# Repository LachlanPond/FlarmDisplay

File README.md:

# FlarmDisplay
Basic LED Flarm display

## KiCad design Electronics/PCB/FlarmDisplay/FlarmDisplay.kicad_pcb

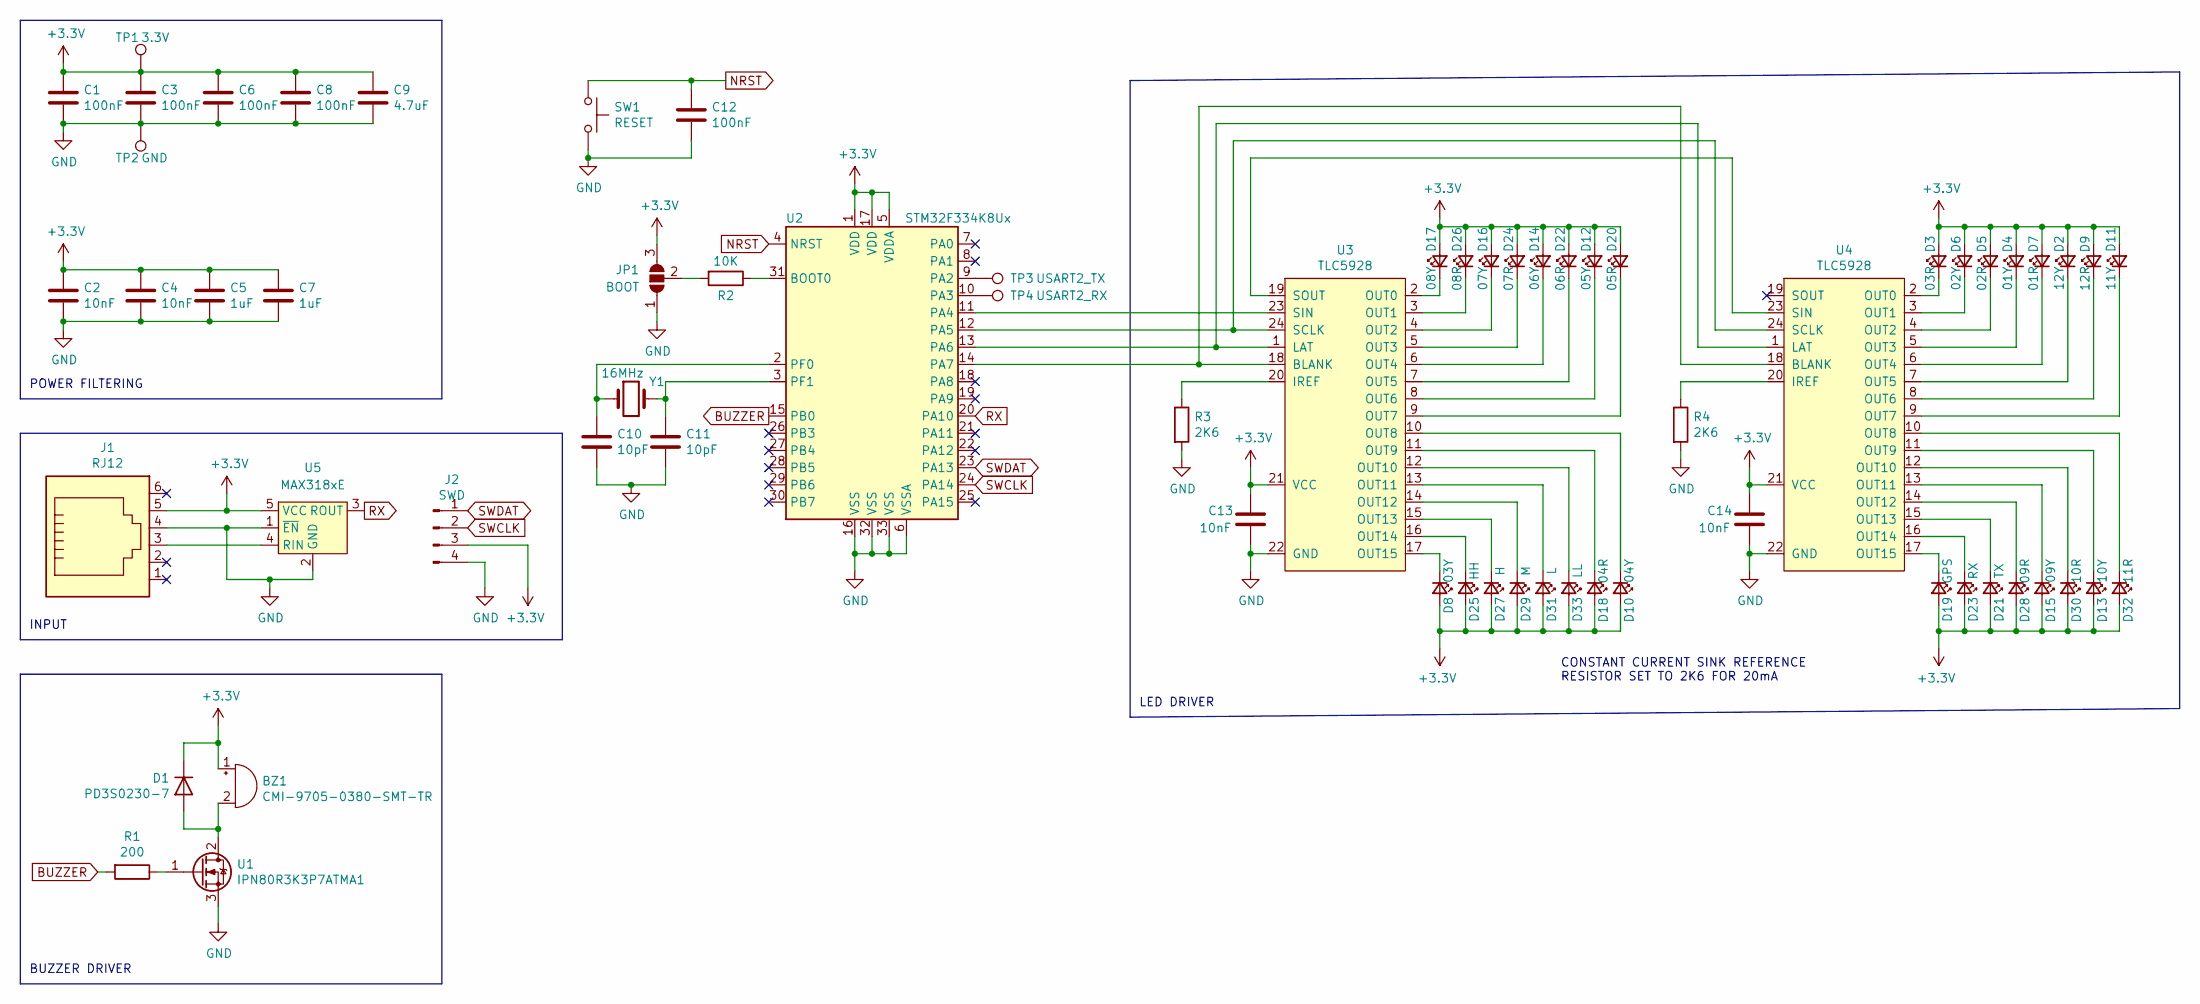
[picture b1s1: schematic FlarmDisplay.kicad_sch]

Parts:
BZ1: CMI-9705-0380-SMT-TR
C1, C3, C6, C8, C12: 100nF; C_0402_1005Metric
C2, C4, C13, C14: 10nF; C_0402_1005Metric
C5, C7: 1uF; C_0402_1005Metric
C9: 4.7uF; C_0805_2012Metric
C10, C11: 10pF; C_0402_1005Metric
D1: PD3S0230-7; POWERDI323
D2: 12Y; LED_0805_2012Metric
D3: 03R; LED_0805_2012Metric
D4: 01Y; LED_0805_2012Metric
D5: 02R; LED_0805_2012Metric
D6: 02Y; LED_0805_2012Metric
D7: 01R; LED_0805_2012Metric
D8: 03Y; LED_0805_2012Metric
D9: 12R; LED_0805_2012Metric
D10: 04Y; LED_0805_2012Metric
D11: 11Y; LED_0805_2012Metric
D12: 05Y; LED_0805_2012Metric
D13: 10Y; LED_0805_2012Metric
D14: 06Y; LED_0805_2012Metric
D15: 09Y; LED_0805_2012Metric
D16: 07Y; LED_0805_2012Metric
D17: 08Y; LED_0805_2012Metric
D18: 04R; LED_0805_2012Metric
D19: GPS; LED_0805_2012Metric
D20: 05R; LED_0805_2012Metric
D21: TX; LED_0805_2012Metric
D22: 06R; LED_0805_2012Metric
D23: RX; LED_0805_2012Metric
D24: 07R; LED_0805_2012Metric
D25: HH; LED_0805_2012Metric
D26: 08R; LED_0805_2012Metric
D27: H; LED_0805_2012Metric
D28: 09R; LED_0805_2012Metric
D29: M; LED_0805_2012Metric
D30: 10R; LED_0805_2012Metric
D31: L; LED_0805_2012Metric
D32: 11R; LED_0805_2012Metric
D33: LL; LED_0805_2012Metric
J1: RJ12; RJE231660413T
J2: SWD; PinHeader_1x04_P2.54mm_Vertical
JP1: BOOT; SolderJumper-3_P1.3mm_Open_RoundedPad1.0x1.5mm
R1: 200; R_0402_1005Metric
R2: 10K; R_0402_1005Metric
R3, R4: 2K6; R_0402_1005Metric
SW1: RESET; SMT_J
TP1: 3.3V; TestPoint_Pad_D2.0mm
TP2: GND; TestPoint_Pad_D2.0mm
TP3: USART2_TX; TestPoint_Pad_D2.0mm
TP4: USART2_RX; TestPoint_Pad_D2.0mm
U1: IPN80R3K3P7ATMA1; SOT-223-3_TabPin2
U2: STM32F334K8Ux; QFN-32-1EP_5x5mm_P0.5mm_EP3.45x3.45mm
U3, U4: TLC5928; VQFN-24-1EP_4x4mm_P0.5mm_EP2.45x2.45mm
U5: MAX318xE; SOT-23-5
Y1: 16MHz; Crystal_SMD_3225-4Pin_3.2x2.5mm

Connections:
+3V3: BZ1.1 (-), C1.1, C2.1, C3.1, C4.1, C5.1, C6.1, C7.1, C8.1, C9.1, C13.1, C14.1, D1.1 (K), D2.2 (A), D3.2 (A), D4.2 (A), D5.2 (A), D6.2 (A), D7.2 (A), D8.2 (A), D9.2 (A), D10.2 (A), D11.2 (A), D12.2 (A), D13.2 (A), D14.2 (A), D15.2 (A), D16.2 (A), D17.2 (A), D18.2 (A), D19.2 (A), D20.2 (A), D21.2 (A), D22.2 (A), D23.2 (A), D24.2 (A), D25.2 (A), D26.2 (A), D27.2 (A), D28.2 (A), D29.2 (A), D30.2 (A), D31.2 (A), D32.2 (A), D33.2 (A), J1.5, J2.3, JP1.3 (B), TP1.1, U2.1 (VDD), U2.5 (VDDA), U2.17 (VDD), U3.21 (VCC), U4.21 (VCC), U5.5 (VCC); also elsewhere on the board
BUZZER: R1.2, U2.15 (PB0)
GND: C1.2, C2.2, C3.2, C4.2, C5.2, C6.2, C7.2, C8.2, C9.2, C10.2, C11.2, C12.2, C13.2, C14.2, J1.4, J2.4, JP1.1 (A), R3.2, R4.2, SW1.2, TP2.1, U1.3, U2.6 (VSSA), U2.16 (VSS), U2.32 (VSS), U2.33 (VSS), U3.22 (GND), U4.22 (GND), U5.1 (~EN), U5.2 (GND)
NRST: C12.1, SW1.1, U2.4 (NRST)
unnamed: BZ1.2 (+), D1.2 (A), U1.2
unnamed: C10.1, U2.2 (PF0), Y1.1
unnamed: C11.1, U2.3 (PF1), Y1.2
unnamed: D2.1 (K), U4.7 (OUT5)
unnamed: D3.1 (K), U4.2 (OUT0)
unnamed: D4.1 (K), U4.5 (OUT3)
unnamed: D5.1 (K), U4.4 (OUT2)
unnamed: D6.1 (K), U4.3 (OUT1)
unnamed: D7.1 (K), U4.6 (OUT4)
unnamed: D8.1 (K), U3.17 (OUT15)
unnamed: D9.1 (K), U4.8 (OUT6)
unnamed: D10.1 (K), U3.10 (OUT8)
unnamed: D11.1 (K), U4.9 (OUT7)
unnamed: D12.1 (K), U3.8 (OUT6)
unnamed: D13.1 (K), U4.11 (OUT9)
unnamed: D14.1 (K), U3.6 (OUT4)
unnamed: D15.1 (K), U4.13 (OUT11)
unnamed: D16.1 (K), U3.4 (OUT2)
unnamed: D17.1 (K), U3.2 (OUT0)
unnamed: D18.1 (K), U3.11 (OUT9)
unnamed: D19.1 (K), U4.17 (OUT15)
unnamed: D20.1 (K), U3.9 (OUT7)
unnamed: D21.1 (K), U4.15 (OUT13)
unnamed: D22.1 (K), U3.7 (OUT5)
unnamed: D23.1 (K), U4.16 (OUT14)
unnamed: D24.1 (K), U3.5 (OUT3)
unnamed: D25.1 (K), U3.16 (OUT14)
unnamed: D26.1 (K), U3.3 (OUT1)
unnamed: D27.1 (K), U3.15 (OUT13)
unnamed: D28.1 (K), U4.14 (OUT12)
unnamed: D29.1 (K), U3.14 (OUT12)
unnamed: D30.1 (K), U4.12 (OUT10)
unnamed: D31.1 (K), U3.13 (OUT11)
unnamed: D32.1 (K), U4.10 (OUT8)
unnamed: D33.1 (K), U3.12 (OUT10)
unnamed: J1.3, U5.4 (RIN)
unnamed: R1.1, U1.1
unnamed: R2.1, U2.31 (BOOT0)
unnamed: JP1.2 (C), R2.2
unnamed: R3.1, U3.20 (IREF)
unnamed: R4.1, U4.20 (IREF)
unnamed 45: TP3.1, U2.9 (PA2); also elsewhere on the board
unnamed 46: TP4.1, U2.10 (PA3); also elsewhere on the board
unnamed: U2.11 (PA4), U3.23 (SIN)
unnamed: U2.12 (PA5), U3.24 (SCLK), U4.24 (SCLK)
unnamed: U2.13 (PA6), U3.1 (LAT), U4.1 (LAT)
unnamed: U2.14 (PA7), U3.18 (BLANK), U4.18 (BLANK)
unnamed: U3.19 (SOUT), U4.23 (SIN)
RX: U2.20 (PA10), U5.3 (ROUT)
SWCLK: J2.2, U2.24 (PA14)
SWDAT: J2.1, U2.23 (PA13)

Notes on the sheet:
INPUT
LED DRIVER
POWER FILTERING
BUZZER DRIVER
CONSTANT CURRENT SINK REFERENCE RESISTOR SET TO 2K6 FOR 20mA

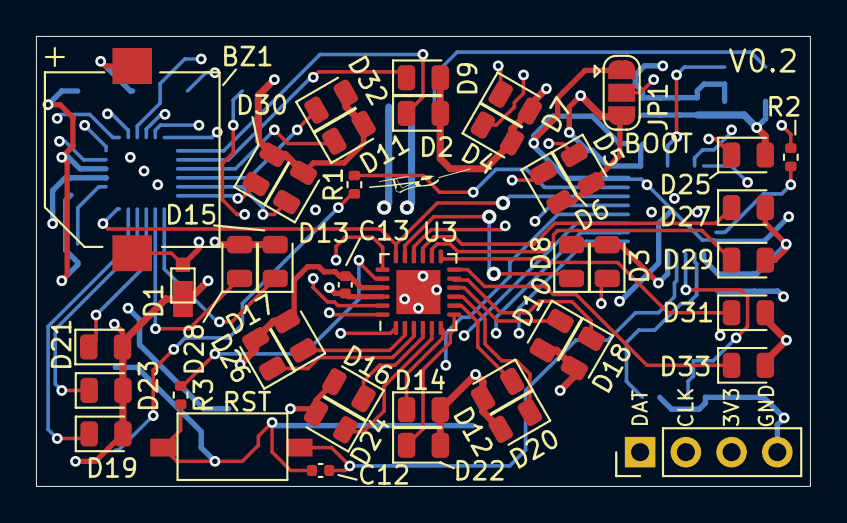
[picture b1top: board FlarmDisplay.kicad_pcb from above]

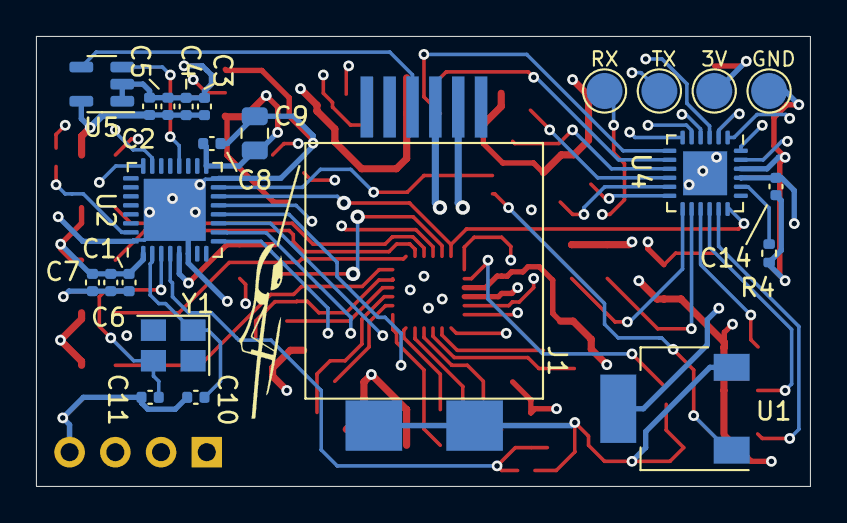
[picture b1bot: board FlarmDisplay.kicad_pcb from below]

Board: 4 copper layers, 43.0 x 25.0 mm, 66 parts (23 on the bottom side), 55 nets.

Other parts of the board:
3V: 3.3V; TestPoint_Pad_D2.0mm
RX: USART2_RX; TestPoint_Pad_D2.0mm
TX: USART2_TX; TestPoint_Pad_D2.0mm

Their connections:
+3V3: 3V.1; also elsewhere on the board
unnamed 45: TX.1; also elsewhere on the board
unnamed 46: RX.1; also elsewhere on the board

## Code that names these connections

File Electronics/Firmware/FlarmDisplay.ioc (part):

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Mcu.Name=STM32F334K(4-6-8)Ux
Mcu.Package=UFQFPN32
Mcu.UserName=STM32F334K8Ux
PA10.Mode=Asynchronous
PA10.Signal=USART1_RX
PA13.Signal=SYS_JTMS-SWDIO
PA14.Signal=SYS_JTCK-SWCLK
PA2.Mode=Asynchronous
PA2.Signal=USART2_TX
PA3.Mode=Asynchronous
PA3.Signal=USART2_RX
PA4.GPIOParameters=PinState,GPIO_PuPd,GPIO_Label
PA4.GPIO_Label=SIN
PA4.GPIO_PuPd=GPIO_PULLDOWN
PA4.PinState=GPIO_PIN_RESET
PA4.Signal=GPIO_Output
PA5.GPIOParameters=PinState,GPIO_PuPd,GPIO_Label
PA5.GPIO_Label=SCLK
PA5.GPIO_PuPd=GPIO_PULLDOWN
PA5.PinState=GPIO_PIN_RESET
PA5.Signal=GPIO_Output
PA6.GPIOParameters=PinState,GPIO_PuPd,GPIO_Label
PA6.GPIO_Label=LAT
PA6.GPIO_PuPd=GPIO_PULLDOWN
PA6.PinState=GPIO_PIN_RESET
PA6.Signal=GPIO_Output
PA7.GPIOParameters=PinState,GPIO_PuPd,GPIO_Label
PA7.GPIO_Label=BLANK
PA7.GPIO_PuPd=GPIO_PULLDOWN
PA7.PinState=GPIO_PIN_RESET
PA7.Signal=GPIO_Output
PA9.Mode=Asynchronous
PA9.Signal=USART1_TX
PB0.GPIOParameters=PinState,GPIO_PuPd,GPIO_Label
PB0.GPIO_Label=BUZZER
PB0.GPIO_PuPd=GPIO_PULLDOWN
PB0.PinState=GPIO_PIN_RESET
PB0.Signal=GPIO_Output
PF0\ /\ OSC_IN.Mode=HSE-External-Oscillator
PF0\ /\ OSC_IN.Signal=RCC_OSC_IN
PF1\ /\ OSC_OUT.Mode=HSE-External-Oscillator
PF1\ /\ OSC_OUT.Signal=RCC_OSC_OUT
RCC.HSEPLLFreq_Value=16000000
RCC.HSE_VALUE=16000000
RCC.SYSCLKFreq_VALUE=64000000
RCC.SYSCLKSourceVirtual=RCC_SYSCLKSOURCE_PLLCLK
board=custom

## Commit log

2022-05-14 Majority of schematic complete
2022-05-15 Initial schematic version complete
2022-05-17 Started work on PCB, most placement done
2022-05-20 Latest
2022-05-20 Completed routing, main silk items, 3D models still to go
2022-05-21 Completed v1.0
2022-05-22 Started work on NMEA test scripts
2022-05-23 Started PFLAA test script
2022-05-24 Completed basic PFLAA test script
2022-05-25 Started PFLAE test script
2022-05-27 Updated PCB to v0.2
2022-06-11 Basic firmware LED test working
2022-06-12 Progress on error packet handling
2024-04-20 Started developing the firmare in Rust
